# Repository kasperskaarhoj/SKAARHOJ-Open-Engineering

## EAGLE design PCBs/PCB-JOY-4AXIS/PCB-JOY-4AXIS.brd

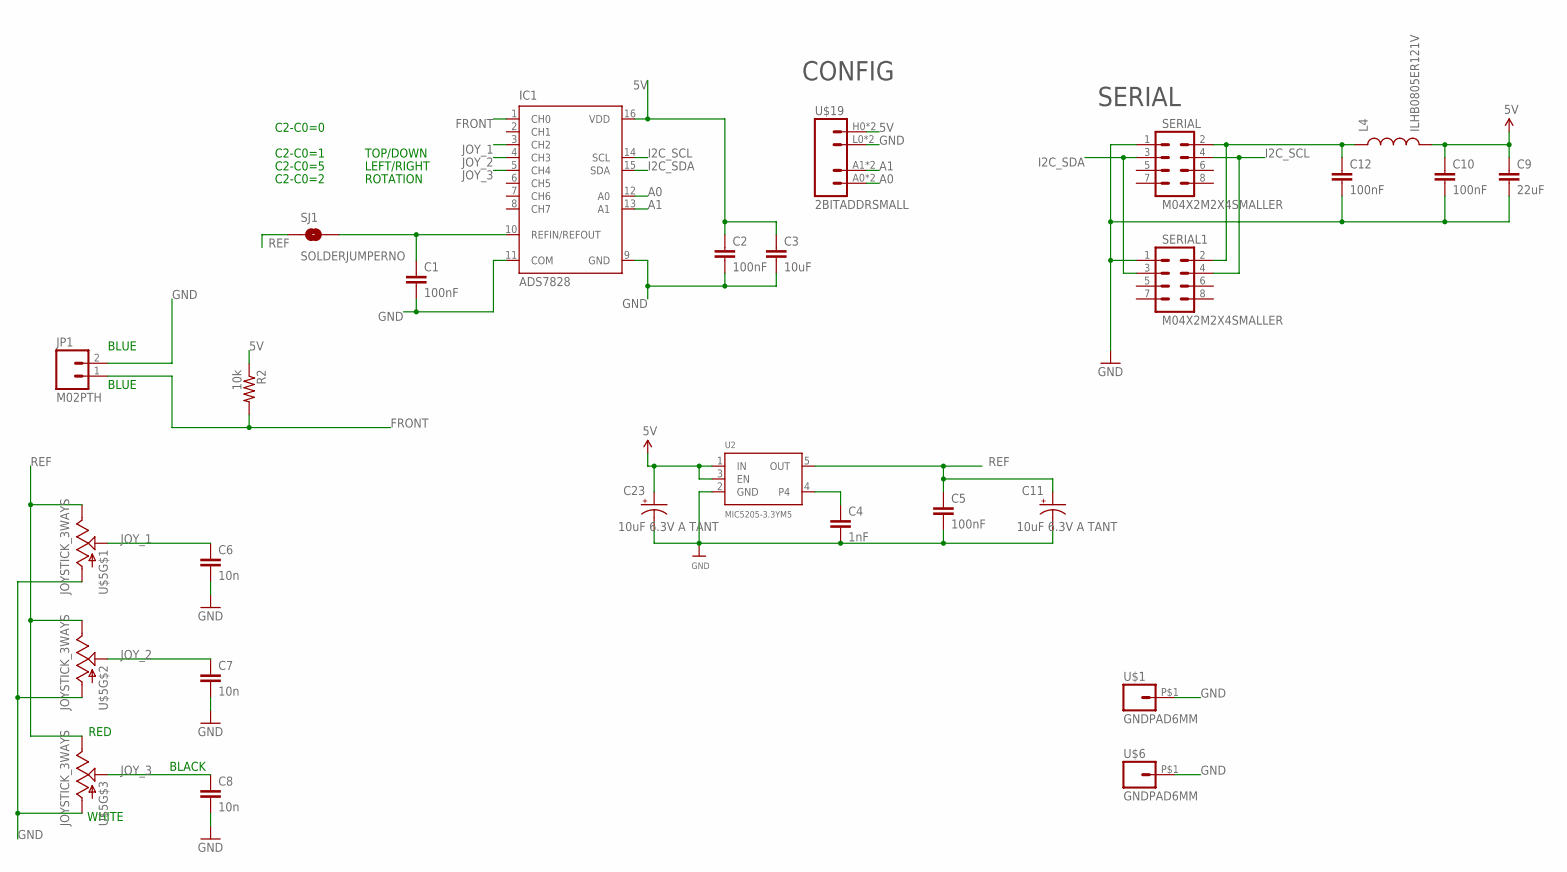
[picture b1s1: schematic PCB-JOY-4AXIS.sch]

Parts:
C1, C2, C5, C10, C12: 100nF; 0603-CAP
C3: 10uF; 0805
C4: 1nF; 0603-CAP
C6, C7, C8: 10n; 0603-CAP
C9: 22uF; 0805
C11, C23: 10uF 6.3V A TANT; EIA3216
IC1: ADS7828; TSSOP16-PW
JP1: M02PTH; 1X02
L4: ILHB0805ER121V; 0805
R2: 10k; 0603-RES
SERIAL, SERIAL1: M04X2M2X4SMALLER; M2X4SMALLER
SJ1: SOLDERJUMPERNO; SJ_2S-NO
U2: MIC5205-3.3YM5; SOT23-5
U$1, U$6: GNDPAD6MM; 3.2MMPAD6MM
U$5: JOYSTICK_3WAYS; JOYSTICK
U$19: 2BITADDRSMALL; 2BITADDR_SMALL

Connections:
5V: C2.1, C3.1, C9.1, C10.1, C23.A (+), IC1.16 (VDD), L4.2, R2.1, U2.1 (IN), U2.3 (EN), U$19.H0 (VCC), U$19.H1 (VCC)
5V_AD: C1.1, IC1.10 (REFIN/REFOUT), SJ1.2
A0: IC1.12 (A0), U$19.A0 (A1), U$19.AS0 (A1)
A1: IC1.13 (A1), U$19.A1 (A2), U$19.AS1 (A2)
ARD_5V: C12.1, L4.1, SERIAL.2, SERIAL1.2
FRONT: IC1.1 (CH0), JP1.1, R2.2
GND: C1.2, C2.2, C3.2, C4.2, C5.2, C6.2, C7.2, C8.2, C9.2, C10.2, C11.C (-), C12.2, C23.C (-), IC1.9 (GND), IC1.11 (COM), JP1.2, SERIAL.1, SERIAL1.1, U2.2 (GND), U$1.P$1, U$5.LR_COM (A), U$5.ROT_COM (A), U$5.UD_COM (A), U$6.P$1, U$19.L0 (GND), U$19.L1 (GND)
I2C_SCL: IC1.14 (SCL), SERIAL.4, SERIAL1.4
I2C_SDA: IC1.15 (SDA), SERIAL.3, SERIAL1.3
JOY_1: C6.1, IC1.3 (CH2), U$5.LR_C (S)
JOY_2: C7.1, IC1.4 (CH3), U$5.UD_C (S)
JOY_3: C8.1, IC1.5 (CH4), U$5.ROT_C (S)
unnamed: C4.1, U2.4
REF: C5.1, C11.A (+), SJ1.1, U2.5 (OUT), U$5.LR_V (E), U$5.ROT_V (E), U$5.UD_V (E)

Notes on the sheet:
CONFIG
TOP/DOWN
LEFT/RIGHT
ROTATION
C2-C0=0
C2-C0=1
C2-C0=5
C2-C0=2
SERIAL
BLACK
RED
WHITE
BLUE

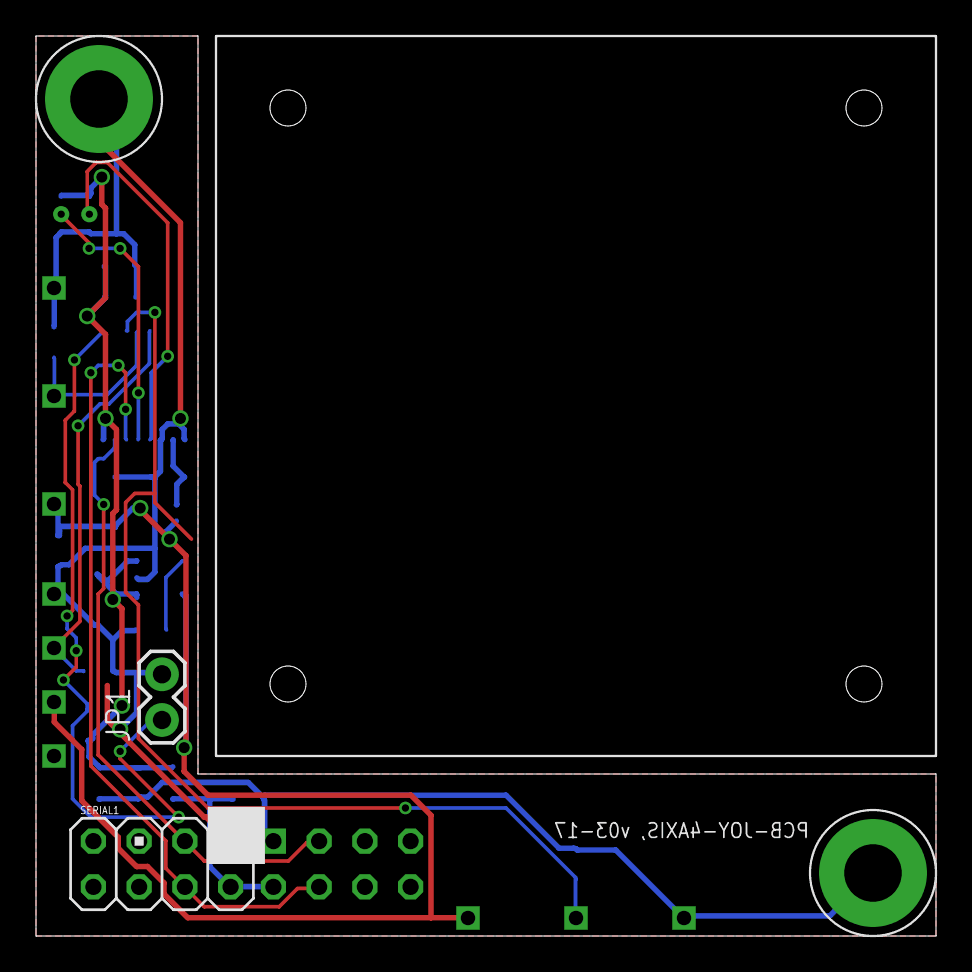
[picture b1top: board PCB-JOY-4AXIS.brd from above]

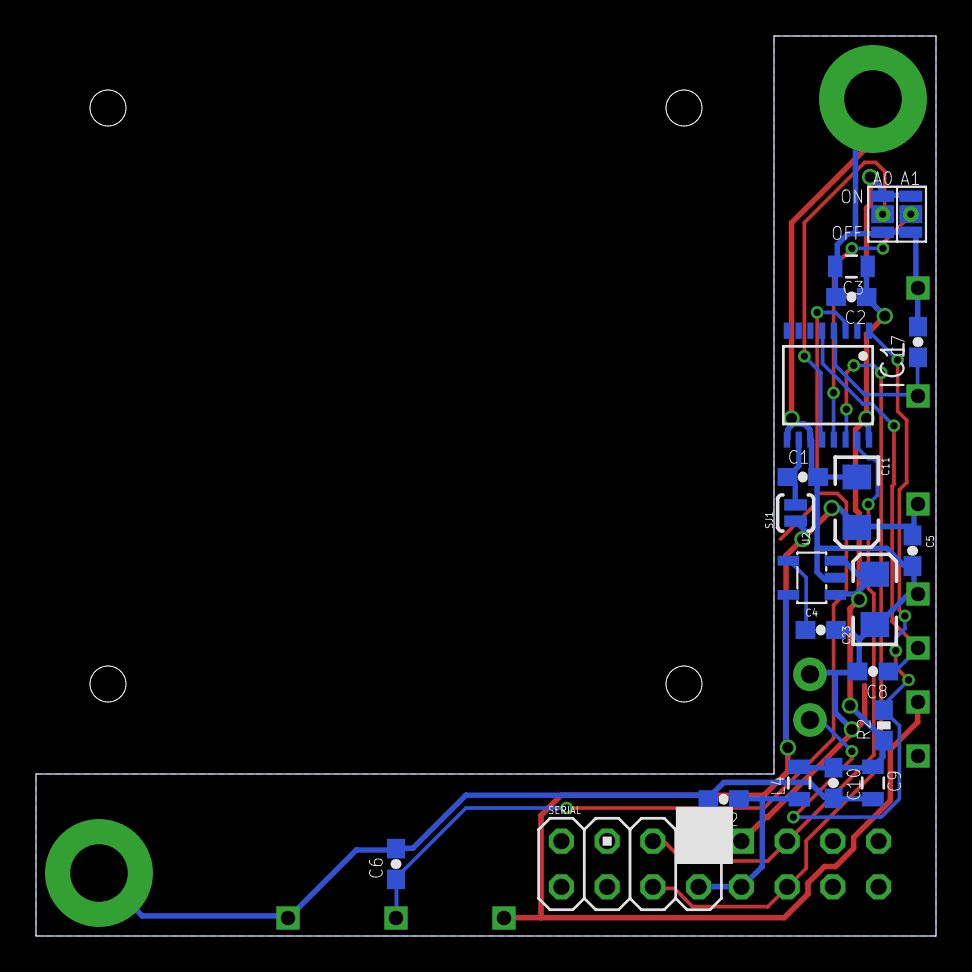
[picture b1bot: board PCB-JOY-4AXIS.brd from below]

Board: 2 copper layers, 50.0 x 50.0 mm, 25 parts (20 on the bottom side), 14 nets.

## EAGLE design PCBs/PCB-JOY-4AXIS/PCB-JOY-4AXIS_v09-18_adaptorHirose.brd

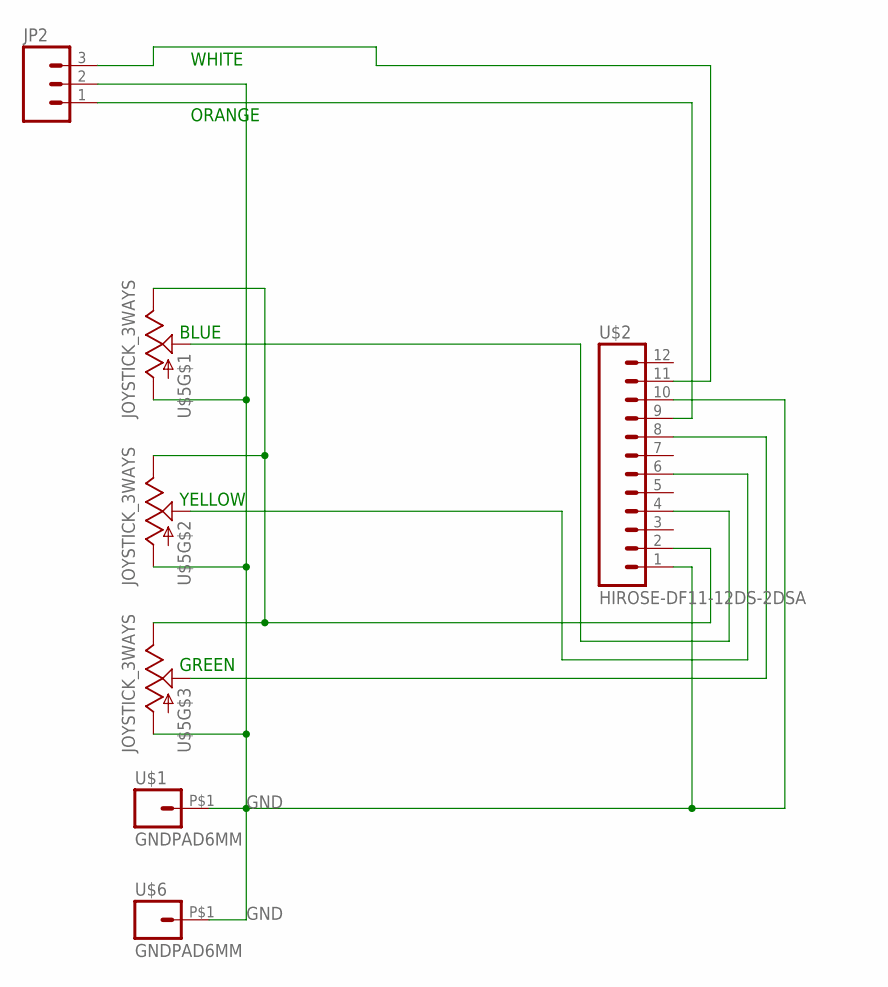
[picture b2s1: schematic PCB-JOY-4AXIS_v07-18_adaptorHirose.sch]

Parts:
JP2: M03PTH; 1X03
U$1, U$6: GNDPAD6MM; 3.2MMPAD6MM
U$2: HIROSE-DF11-12DS-2DSA; 2X6HIROSE_DF11-12DS-2DSA
U$5: JOYSTICK_3WAYS; JOYSTICK

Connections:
GND: JP2.2, U$1.P$1, U$2.1, U$2.10, U$5.LR_COM (A), U$5.ROT_COM (A), U$5.UD_COM (A), U$6.P$1
unnamed: U$2.2, U$5.LR_V (E), U$5.ROT_V (E), U$5.UD_V (E)
unnamed: U$2.4, U$5.LR_C (S)
unnamed: U$2.6, U$5.UD_C (S)
unnamed: U$2.8, U$5.ROT_C (S)
unnamed: JP2.1, U$2.9
unnamed: JP2.3, U$2.11

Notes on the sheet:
GREEN
ORANGE
WHITE
YELLOW
BLUE

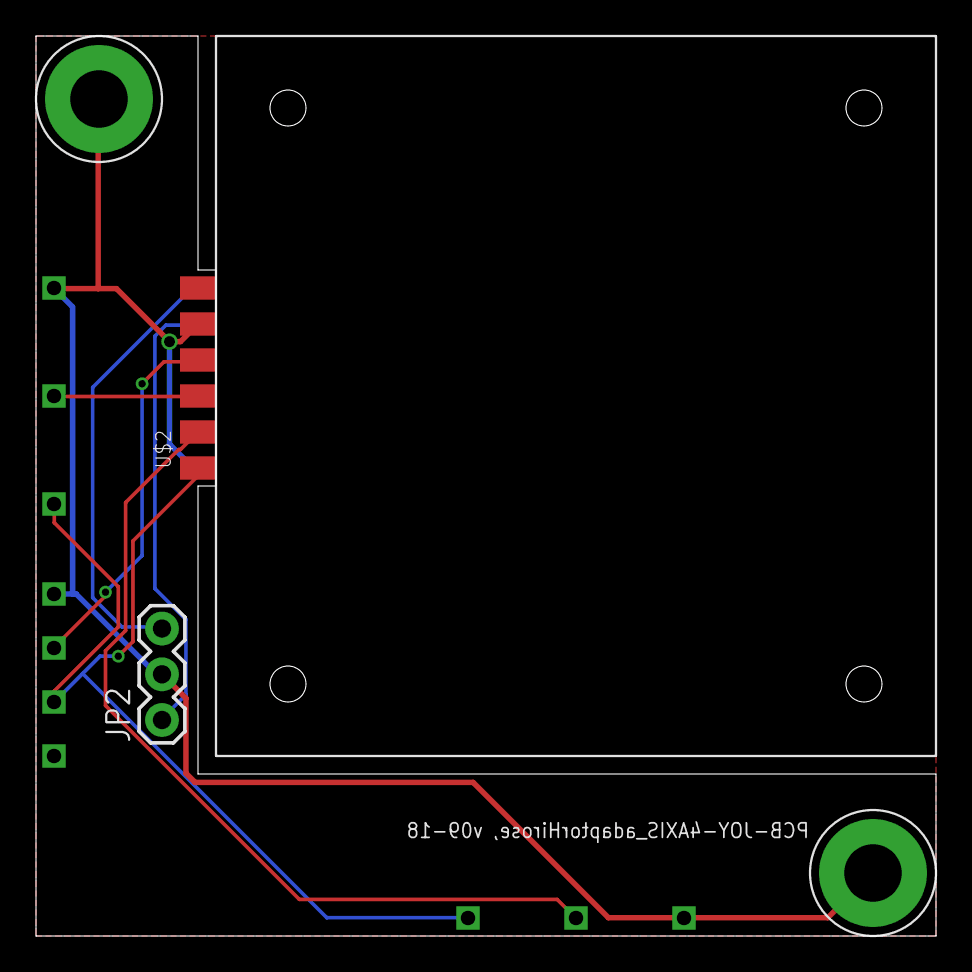
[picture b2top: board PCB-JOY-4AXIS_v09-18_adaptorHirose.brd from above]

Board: 2 copper layers, 50.0 x 50.0 mm, 5 parts (0 on the bottom side), 7 nets.

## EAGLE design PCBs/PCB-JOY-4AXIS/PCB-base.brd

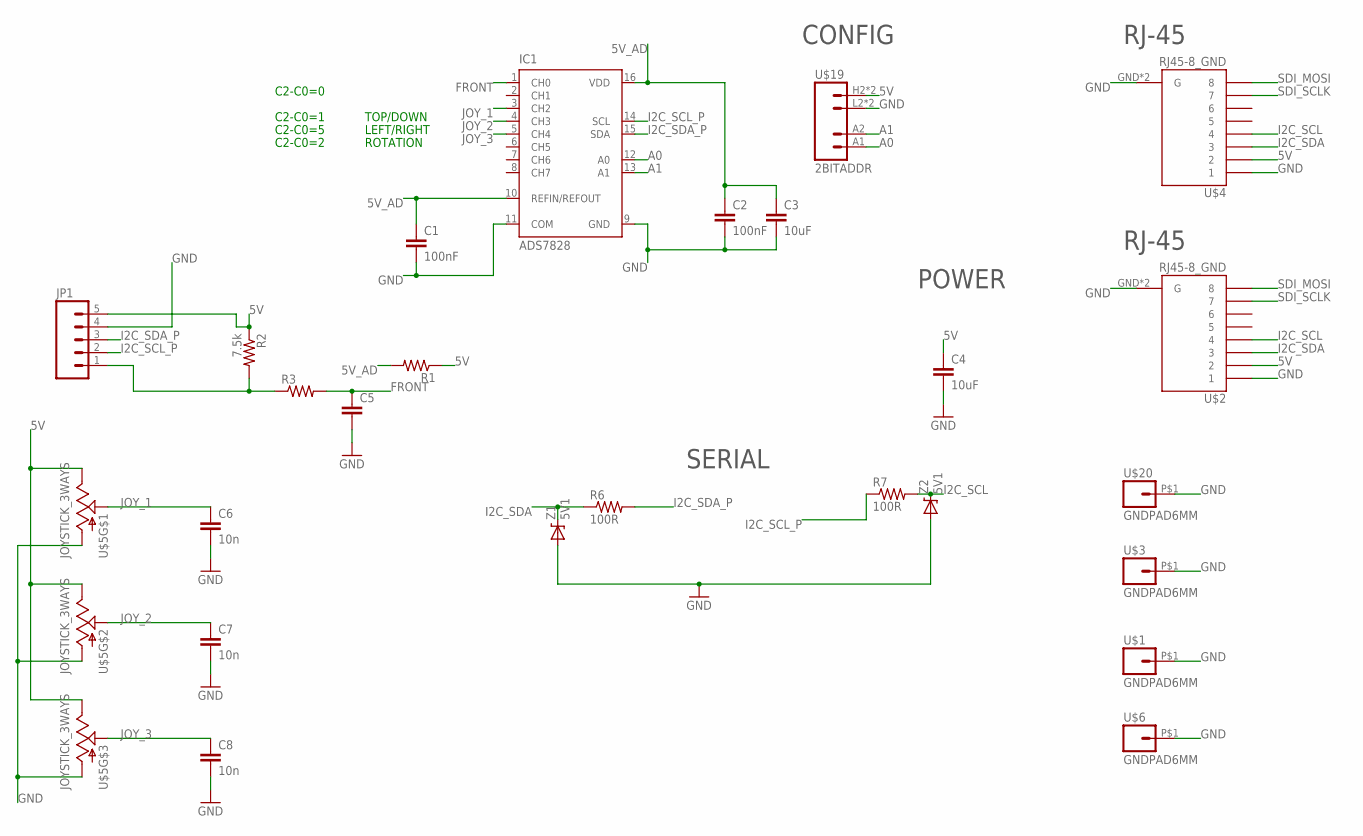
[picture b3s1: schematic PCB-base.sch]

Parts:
C1, C2: 100nF; 0603-CAP
C3, C4: 10uF; 0805
C5: CAP0603-CAP; 0603-CAP
C6, C7, C8: 10n; 0603-CAP
IC1: ADS7828; TSSOP16-PW
JP1: M05PTH; 1X05
R1, R3: RESISTOR0603-RES; 0603-RES
R2: 7.5k; 0603-RES
R6, R7: 100R; 0603-RES
U$1, U$3, U$6, U$20: GNDPAD6MM; 3.2MMPAD6MM
U$2, U$4: RJ45-8_GND
U$5: JOYSTICK_3WAYS; JOYSTICK
U$19: 2BITADDR
Z1, Z2: 5V1; SMB-DIODE

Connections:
5V: C4.1, JP1.5, R1.1, R2.1, U$2.2, U$4.2, U$5.LR_V (E), U$5.ROT_V (E), U$5.UD_V (E), U$19.H2 (VCC), U$19.H3 (VCC)
5V_AD: C1.1, C2.1, C3.1, IC1.10 (REFIN/REFOUT), IC1.16 (VDD), R1.2
A0: IC1.12 (A0), U$19.A1
A1: IC1.13 (A1), U$19.A2
FRONT: C5.1, IC1.1 (CH0), R3.2
GND: C1.2, C2.2, C3.2, C4.2, C5.2, C6.2, C7.2, C8.2, IC1.9 (GND), IC1.11 (COM), JP1.4, U$1.P$1, U$2.1, U$2.GND (G), U$2.GND1 (G), U$3.P$1, U$4.1, U$4.GND (G), U$4.GND1 (G), U$5.LR_COM (A), U$5.ROT_COM (A), U$5.UD_COM (A), U$6.P$1, U$19.L2 (GND), U$19.L3 (GND), U$20.P$1, Z1.A, Z2.A
I2C_SCL: R7.2, U$2.4, U$4.4, Z2.C
I2C_SCL_P: IC1.14 (SCL), JP1.2, R7.1
I2C_SDA: R6.1, U$2.3, U$4.3, Z1.C
I2C_SDA_P: IC1.15 (SDA), JP1.3, R6.2
JOY_1: C6.1, IC1.3 (CH2), U$5.LR_C (S)
JOY_2: C7.1, IC1.4 (CH3), U$5.UD_C (S)
JOY_3: C8.1, IC1.5 (CH4), U$5.ROT_C (S)
unnamed: JP1.1, R2.2, R3.1
SDI_MOSI: U$2.8, U$4.8
SDI_SCLK: U$2.7, U$4.7

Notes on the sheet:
SERIAL
RJ-45
CONFIG
POWER
TOP/DOWN
LEFT/RIGHT
ROTATION
C2-C0=0
C2-C0=1
C2-C0=5
C2-C0=2

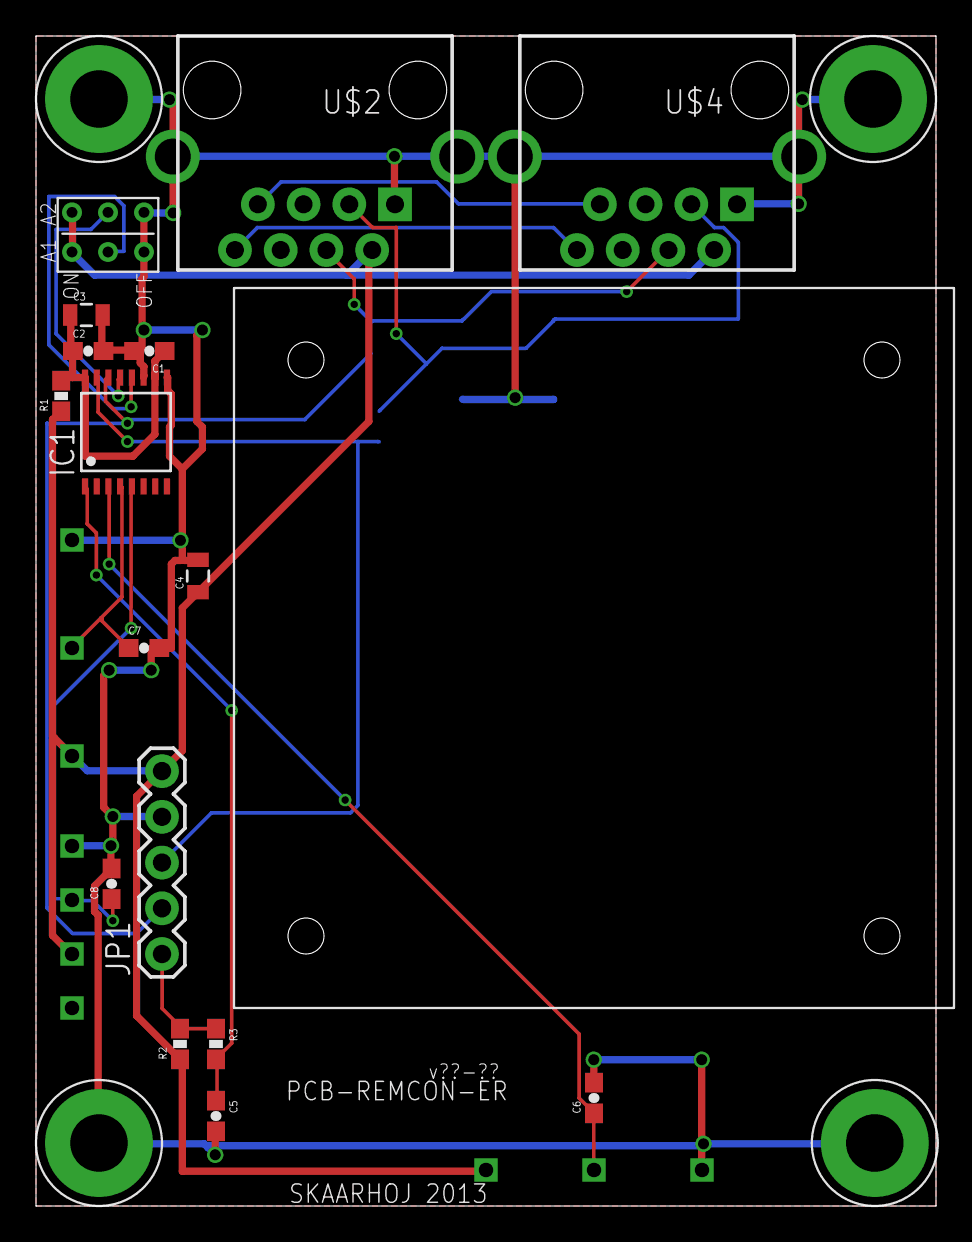
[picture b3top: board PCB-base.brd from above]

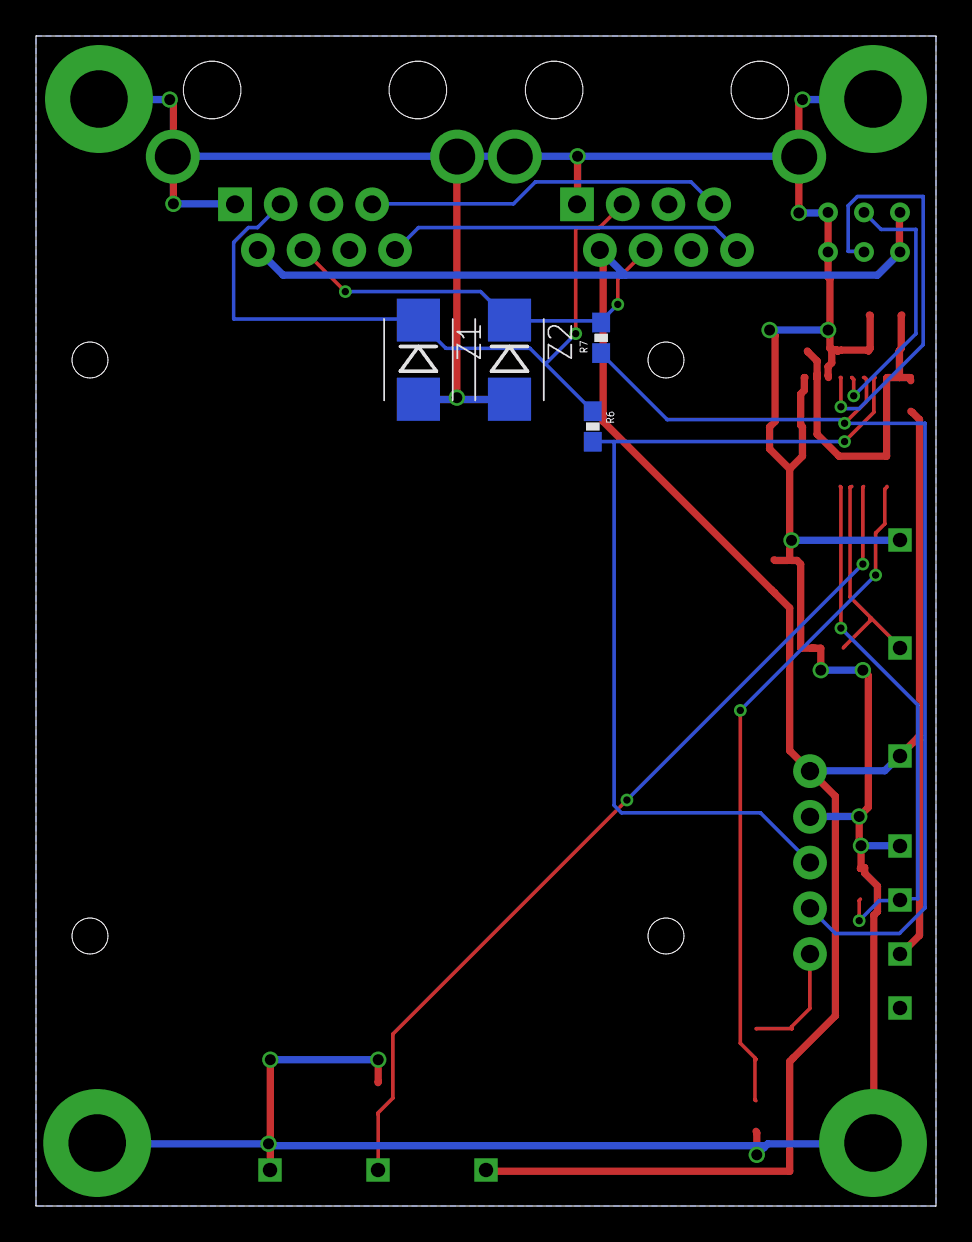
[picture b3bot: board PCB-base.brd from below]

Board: 2 copper layers, 50.0 x 65.0 mm, 25 parts (4 on the bottom side), 16 nets.

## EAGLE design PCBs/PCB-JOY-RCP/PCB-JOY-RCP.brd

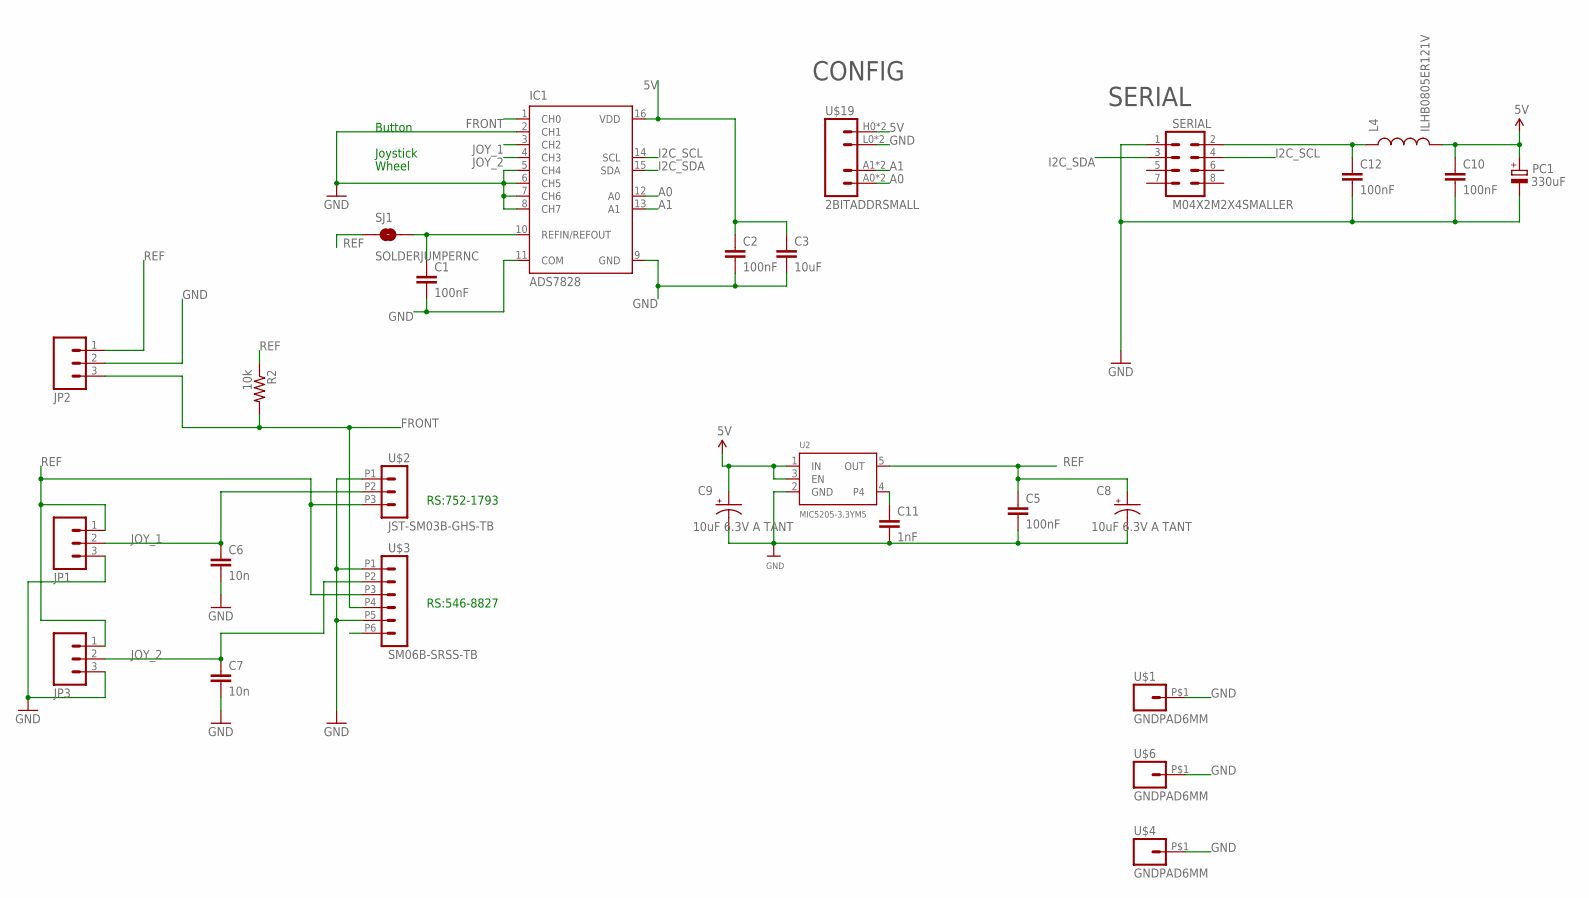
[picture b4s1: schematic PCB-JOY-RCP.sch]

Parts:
C1, C2, C5, C10, C12: 100nF; 0603-CAP
C3: 10uF; 0805
C6, C7: 10n; 0603-CAP
C8, C9: 10uF 6.3V A TANT; EIA3216
C11: 1nF; 0603-CAP
IC1: ADS7828; TSSOP16-PW
JP1, JP2, JP3: M03PTH; 1X03
L4: ILHB0805ER121V; 0805
PC1: 330uF; PANASONIC_D
R2: 10k; 0603-RES
SERIAL: M04X2M2X4SMALLER; M2X4SMALLER
SJ1: SOLDERJUMPERNC; SJ_2S
U2: MIC5205-3.3YM5; SOT23-5
U$1, U$4, U$6: GNDPAD6MM; 3.2MMPAD6MM
U$2: JST-SM03B-GHS-TB
U$3: SM06B-SRSS-TB; JST-SM06B-SRSS-TB
U$19: 2BITADDRSMALL; 2BITADDR_SMALL

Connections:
5V: C2.1, C3.1, C9.A (+), C10.1, IC1.16 (VDD), L4.2, PC1.+, U2.1 (IN), U2.3 (EN), U$19.H0 (VCC), U$19.H1 (VCC)
A0: IC1.12 (A0), U$19.A0 (A1), U$19.AS0 (A1)
A1: IC1.13 (A1), U$19.A1 (A2), U$19.AS1 (A2)
ARD_5V: C12.1, L4.1, SERIAL.2
FRONT: IC1.1 (CH0), JP2.3, R2.2, U$3.P4 (4)
GND: C1.2, C2.2, C3.2, C5.2, C6.2, C7.2, C8.C (-), C9.C (-), C10.2, C11.2, C12.2, IC1.2 (CH1), IC1.5 (CH4), IC1.6 (CH5), IC1.7 (CH6), IC1.8 (CH7), IC1.9 (GND), IC1.11 (COM), JP1.3, JP2.2, JP3.3, PC1.-, SERIAL.1, U2.2 (GND), U$1.P$1, U$2.P1 (1), U$3.P1 (1), U$3.P5 (5), U$4.P$1, U$6.P$1, U$19.L0 (GND), U$19.L1 (GND)
I2C_SCL: IC1.14 (SCL), SERIAL.4
I2C_SDA: IC1.15 (SDA), SERIAL.3
JOY_1: C6.1, IC1.3 (CH2), JP1.2, U$2.P2 (2)
JOY_2: C7.1, IC1.4 (CH3), JP3.2, U$3.P2 (2)
unnamed: C1.1, IC1.10 (REFIN/REFOUT), SJ1.2
unnamed: C11.1, U2.4
REF: C5.1, C8.A (+), JP1.1, JP2.1, JP3.1, R2.1, SJ1.1, U2.5 (OUT), U$2.P3 (3), U$3.P3 (3)

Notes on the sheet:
CONFIG
Joystick
Wheel
Button
SERIAL
RS:546-8827
RS:752-1793

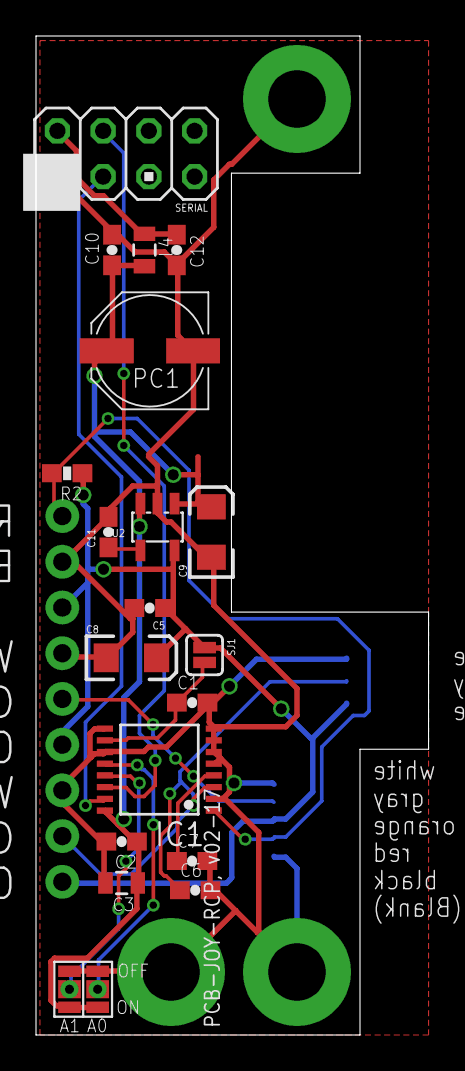
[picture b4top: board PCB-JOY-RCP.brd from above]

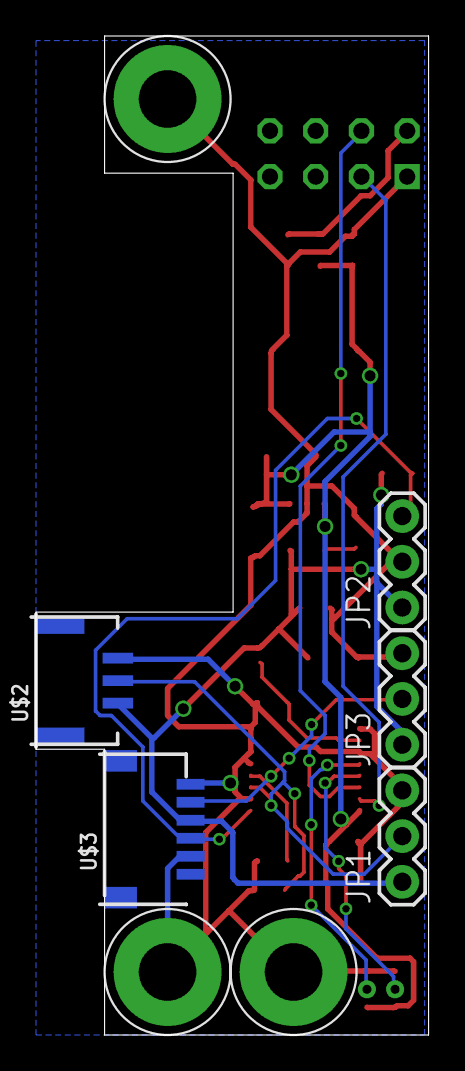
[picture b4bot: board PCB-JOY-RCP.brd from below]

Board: 2 copper layers, 21.8 x 55.5 mm, 27 parts (8 on the bottom side), 13 nets.

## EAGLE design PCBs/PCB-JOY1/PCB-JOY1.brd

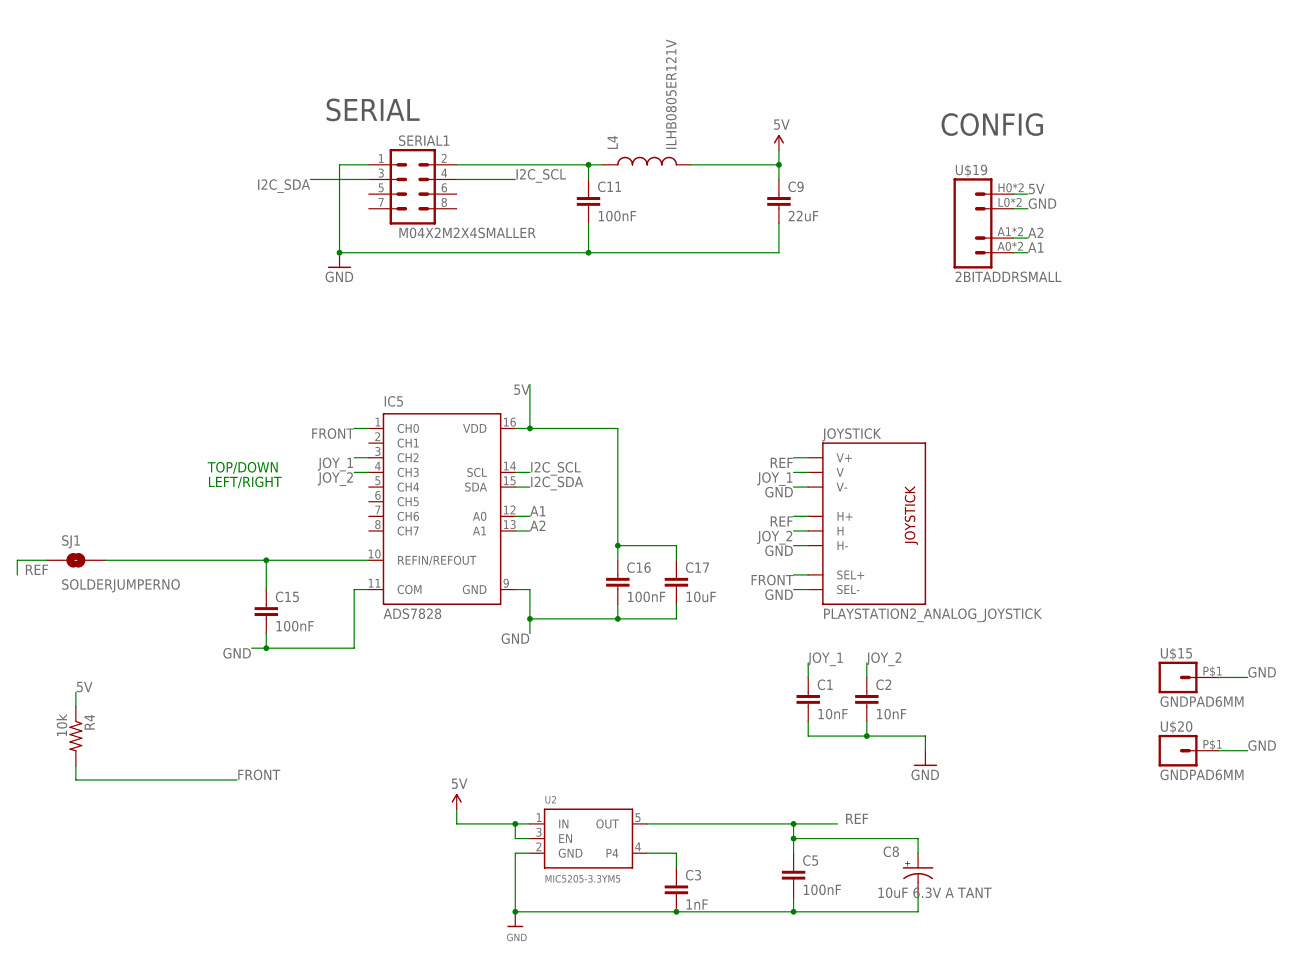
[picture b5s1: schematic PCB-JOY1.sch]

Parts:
C1, C2: 10nF; 0603-CAP
C3: 1nF; 0603-CAP
C5, C11, C15, C16: 100nF; 0603-CAP
C8: 10uF 6.3V A TANT; EIA3216
C9: 22uF; 0805
C17: 10uF; 0805
IC5: ADS7828; TSSOP16-PW
JOYSTICK: PLAYSTATION2_ANALOG_JOYSTICK
L4: ILHB0805ER121V; 0805
R4: 10k; 0603-RES
SERIAL1: M04X2M2X4SMALLER; M2X4SMALLER
SJ1: SOLDERJUMPERNO; SJ_2S-NO
U2: MIC5205-3.3YM5; SOT23-5
U$15, U$20: GNDPAD6MM; 3.2MMPAD6MM
U$19: 2BITADDRSMALL; 2BITADDR_SMALL

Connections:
5V: C9.1, C16.1, C17.1, IC5.16 (VDD), L4.2, R4.1, U2.1 (IN), U2.3 (EN), U$19.H0 (VCC), U$19.H1 (VCC)
5V_AD: C15.1, IC5.10 (REFIN/REFOUT), SJ1.2
A1: IC5.12 (A0), U$19.A0 (A1), U$19.AS0 (A1)
A2: IC5.13 (A1), U$19.A1 (A2), U$19.AS1 (A2)
FRONT: IC5.1 (CH0), JOYSTICK.B1A (SEL+), R4.2
GND: C1.2, C2.2, C3.2, C5.2, C8.C (-), C9.2, C11.2, C15.2, C16.2, C17.2, IC5.9 (GND), IC5.11 (COM), JOYSTICK.B2A (SEL-), JOYSTICK.H3 (H-), JOYSTICK.V3 (V-), SERIAL1.1, U2.2 (GND), U$15.P$1, U$19.L0 (GND), U$19.L1 (GND), U$20.P$1
I2C_SCL: IC5.14 (SCL), SERIAL1.4
I2C_SDA: IC5.15 (SDA), SERIAL1.3
JOY_1: C1.1, IC5.3 (CH2), JOYSTICK.V2 (V)
JOY_2: C2.1, IC5.4 (CH3), JOYSTICK.H2 (H)
unnamed: C11.1, L4.1, SERIAL1.2
unnamed: C3.1, U2.4
REF: C5.1, C8.A (+), JOYSTICK.H1 (H+), JOYSTICK.V1 (V+), SJ1.1, U2.5 (OUT)

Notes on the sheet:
SERIAL
TOP/DOWN
LEFT/RIGHT
CONFIG

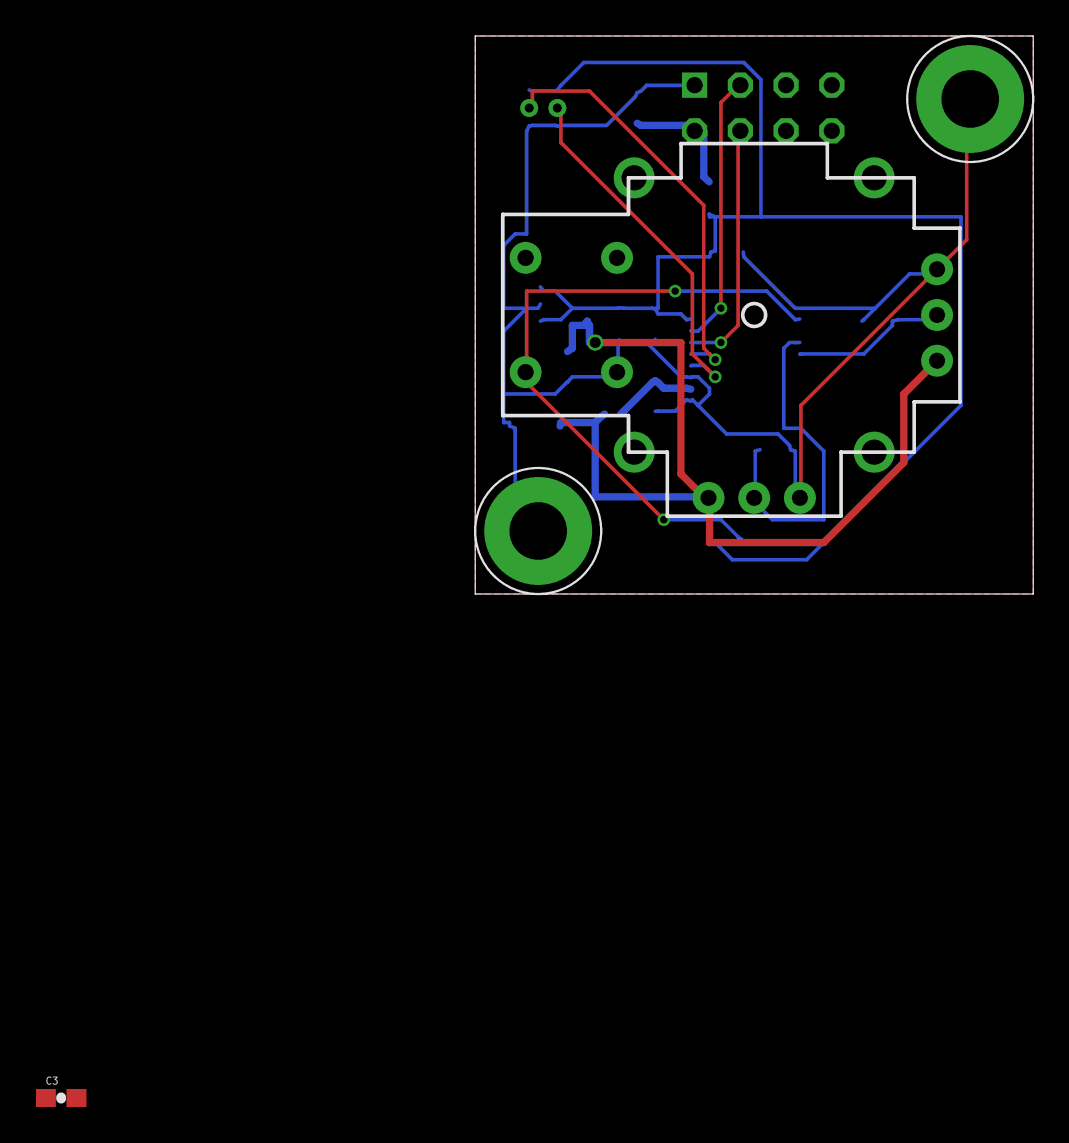
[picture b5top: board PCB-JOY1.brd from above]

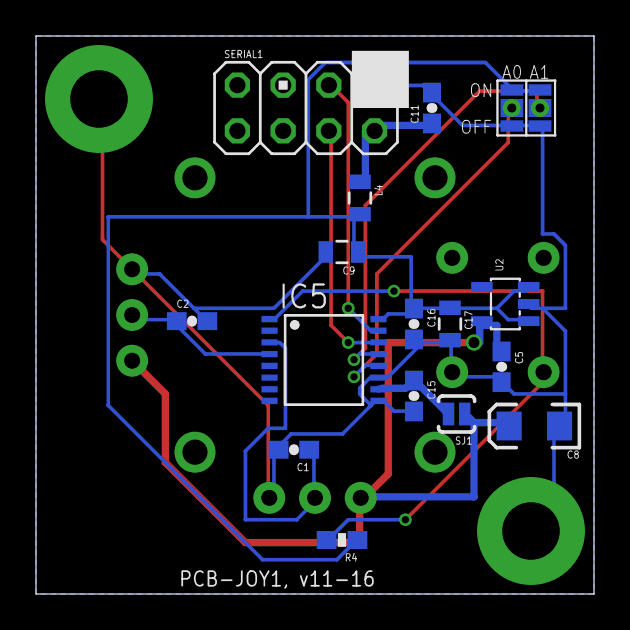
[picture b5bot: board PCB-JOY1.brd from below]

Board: 2 copper layers, 31.0 x 31.0 mm, 20 parts (16 on the bottom side), 13 nets.

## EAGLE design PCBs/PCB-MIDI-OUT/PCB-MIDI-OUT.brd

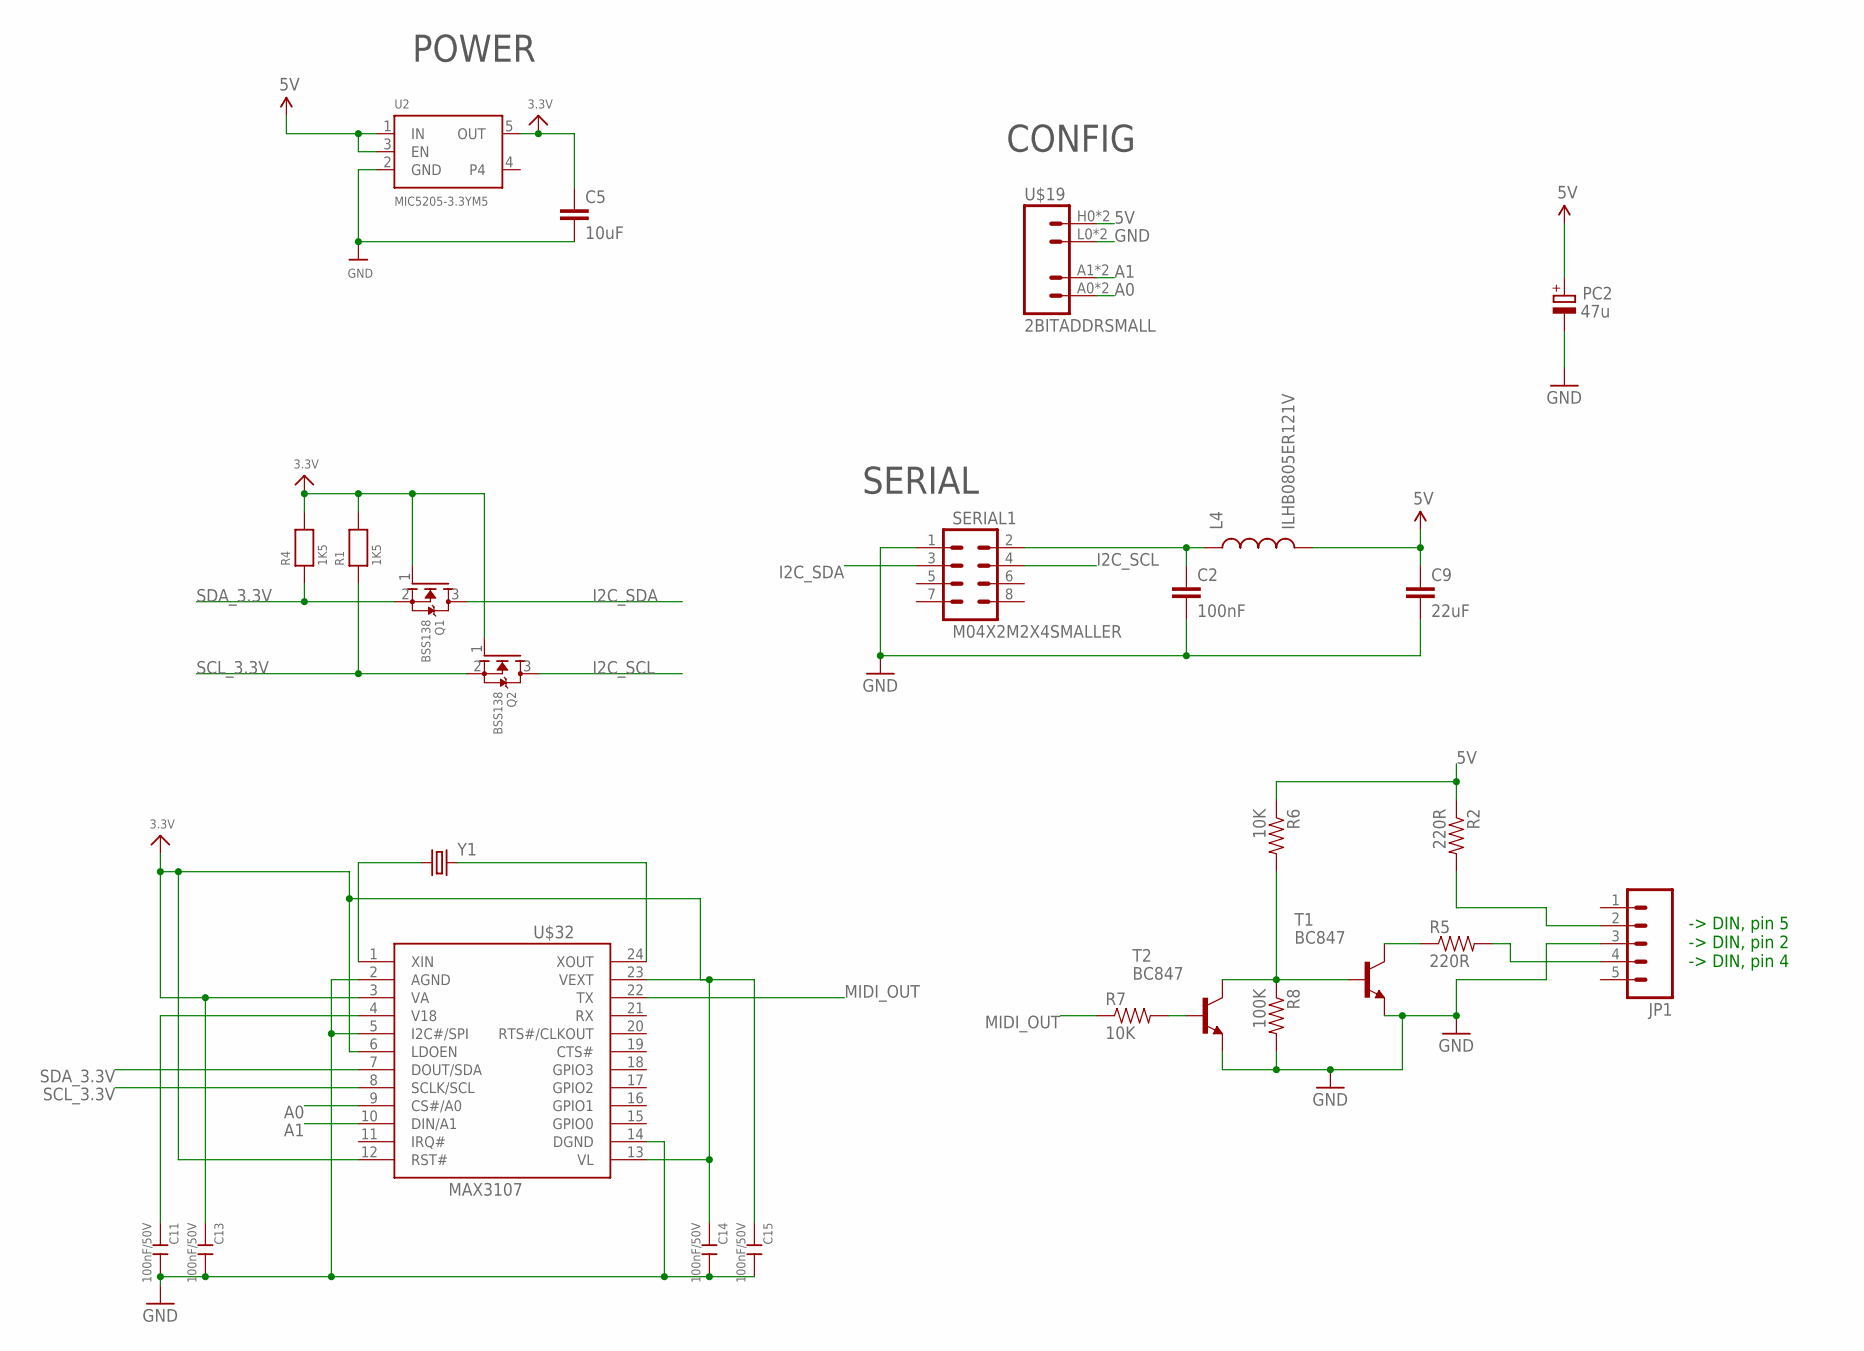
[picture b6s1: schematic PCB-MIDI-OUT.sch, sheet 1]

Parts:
C2: 100nF; 0603-CAP
C5: 10uF; 0805
C9: 22uF; 0805
C11, C13, C14, C15: 100nF/50V; C0603
JP1: M05LOCK; 1X05_LOCK
L4: ILHB0805ER121V; 0805
PC2: 47u; PANASONIC_D
Q1, Q2: BSS138; SOT23-R
R1, R4: 1K5; 0603
R2, R5: 220R; 0603-RES
R6, R7: 10K; 0603-RES
R8: 100K; 0603-RES
SERIAL1: M04X2M2X4SMALLER; M2X4SMALLER
T1, T2: BC847; SOT23
U2: MIC5205-3.3YM5; SOT23-5
U$19: 2BITADDRSMALL; 2BITADDR_SMALL
U$32: MAX3107; SSOP24
Y1: CRYSTALHC49US; HC49US

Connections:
3.3V: C5.1, C13.1, C14.1, C15.1, Q1.1 (G), Q2.1 (G), R1.2, R4.2, U2.5 (OUT), U$32.3 (VA), U$32.6 (LDOEN), U$32.12 (RST#), U$32.13 (VL), U$32.23 (VEXT)
5V: C9.1, L4.2, PC2.+, R2.1, R6.1, U2.1 (IN), U2.3 (EN), U$19.H0 (VCC), U$19.H1 (VCC)
A0: U$19.A0 (A1), U$19.AS0 (A1), U$32.9 (CS#/A0)
A1: U$19.A1 (A2), U$19.AS1 (A2), U$32.10 (DIN/A1)
GND: C2.2, C5.2, C9.2, C11.2, C13.2, C14.2, C15.2, JP1.3, PC2.-, R8.2, SERIAL1.1, T1.2 (E), T2.2 (E), U2.2 (GND), U$19.L0 (GND), U$19.L1 (GND), U$32.2 (AGND), U$32.5 (I2C#/SPI), U$32.14 (DGND)
I2C_SCL: Q2.3 (D), SERIAL1.4
I2C_SDA: Q1.3 (D), SERIAL1.3
MIDI_OUT: R7.1, U$32.22 (TX)
unnamed: C2.1, L4.1, SERIAL1.2
unnamed: R6.2, R8.1, T1.1 (B), T2.3 (C)
unnamed: JP1.2, R2.2
unnamed: C11.1, U$32.4 (V18)
unnamed: R5.1, T1.3 (C)
unnamed: JP1.4, R5.2
unnamed: U$32.1 (XIN), Y1.1
unnamed: R7.2, T2.1 (B)
unnamed: U$32.24 (XOUT), Y1.2
SCL_3.3V: Q2.2 (S), R1.1, U$32.8 (SCLK/SCL)
SDA_3.3V: Q1.2 (S), R4.1, U$32.7 (DOUT/SDA)

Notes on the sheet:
SERIAL
POWER
CONFIG
-> DIN, pin 5 -> DIN, pin 2 -> DIN, pin 4

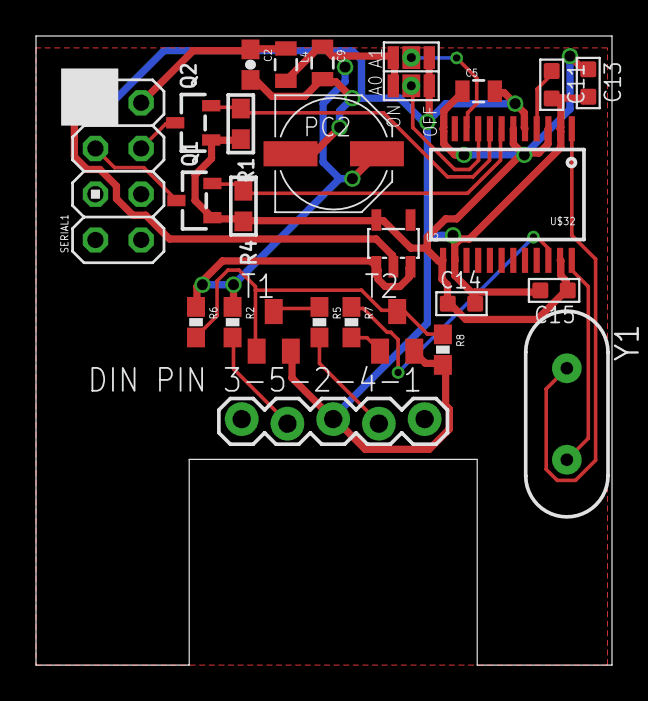
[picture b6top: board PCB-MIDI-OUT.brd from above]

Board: 2 copper layers, 32.0 x 35.0 mm, 26 parts (0 on the bottom side), 19 nets.

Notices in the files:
parts and their libraries:
SparkFun: Licensing: CC v3.0 Share-Alike You are welcome to use this library for commercial purposes.
